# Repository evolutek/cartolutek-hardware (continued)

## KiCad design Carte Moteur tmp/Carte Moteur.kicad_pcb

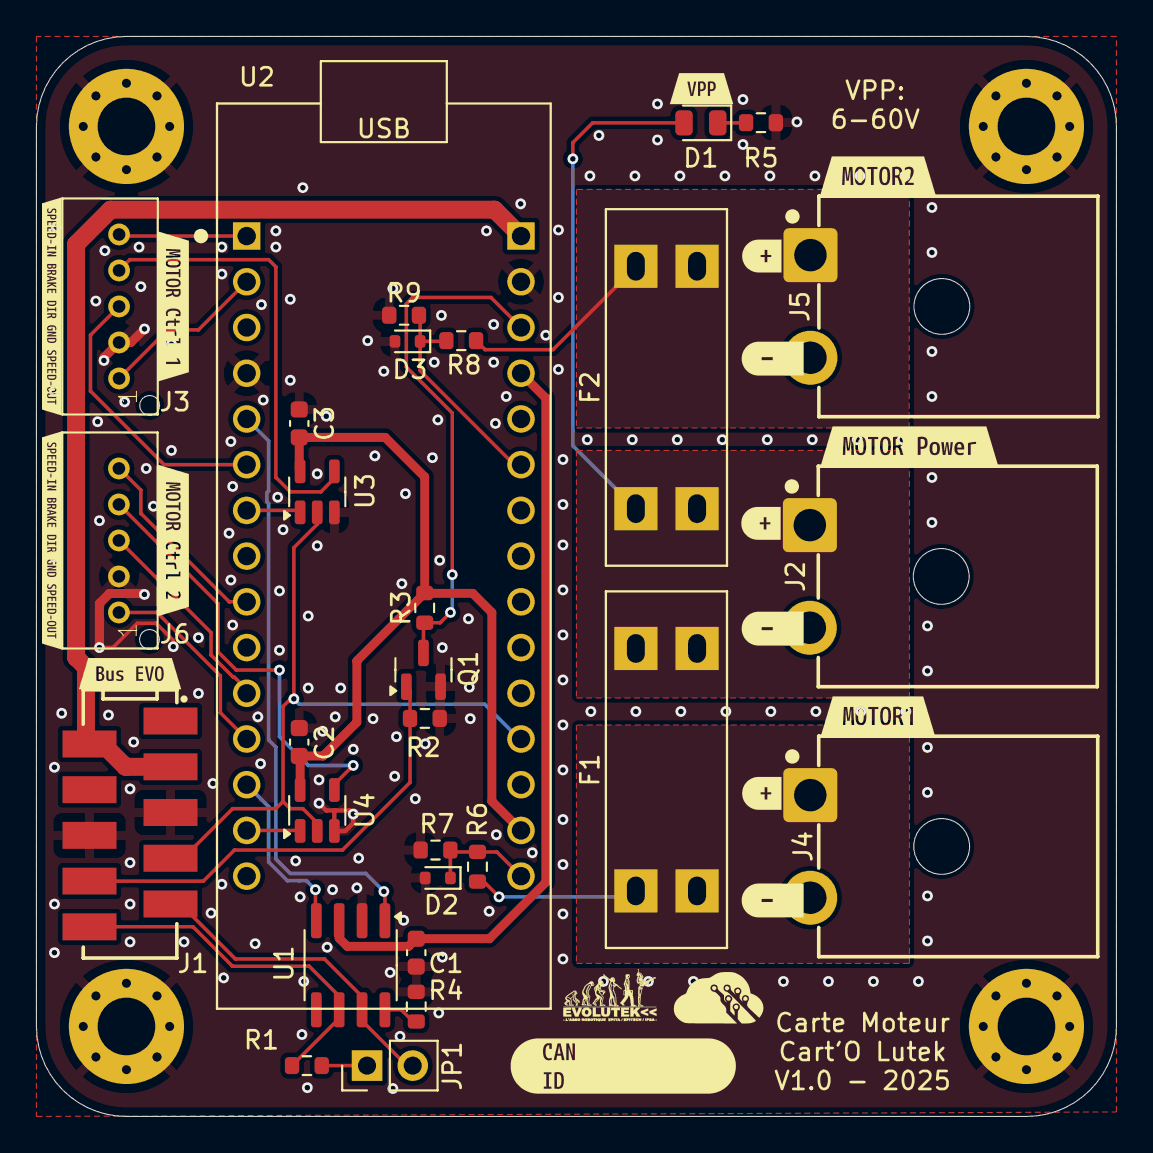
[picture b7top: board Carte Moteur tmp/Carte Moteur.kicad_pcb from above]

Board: 2 copper layers, 60.0 x 60.0 mm, 51 parts (0 on the bottom side), 29 nets.

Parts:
C1, C2, C3: 100nF; C_0603_1608Metric
D1: LED; LED_0805_2012Metric
D2, D3: 3V; D_SOD-523
F1, F2: To determine; FUSE_3557-2
H1, H2, H3, H4: M3; MountingHole_3.2mm_M3_Pad_Via
J1: Bus EVO; 690367281076
J2: Motor PSU; 657002140101
J3, J6: Motor Control; B05B-PASK
J4, J5: Motor; 657002140101
JP1: Jumper_2_Open; PinHeader_1x02_P2.54mm_Vertical
LB1: LOGO; logo-evo-micro
LB2: CAN ID Label
LB3: LOGO; Logo Aisler Micro
Q1: Q_NMOS_GSD; SOT-23
R1: 120; R_0603_1608Metric
R2, R3, R7, R9: 10k; R_0603_1608Metric
R4: 0; R_0603_1608Metric
R5: 2.1k; R_0603_1608Metric
R6, R8: 100k; R_0603_1608Metric
U1: MCP2551-I-SN; SOIC-8_3.9x4.9mm_P1.27mm
U2: NUCLEO-G431KB; MODULE_NUCLEO-32
U3, U4: SN74LVC1G32; SOT-23-5
kibuzzard-6849F6E8: G***; kibuzzard-6849F6E8
kibuzzard-6849F8B2: G***; kibuzzard-6849F8B2
kibuzzard-6849F8DE: G***; kibuzzard-6849F8DE
kibuzzard-6849F74E: G***; kibuzzard-6849F74E
kibuzzard-6849F710: G***; kibuzzard-6849F710
kibuzzard-6849F726: G***; kibuzzard-6849F726
kibuzzard-6849FC70, kibuzzard-6849FC70#2, kibuzzard-6849FC70#3: G***; kibuzzard-6849FC70
kibuzzard-6849FC90, kibuzzard-6849FC90#2, kibuzzard-6849FC90#3: G***; kibuzzard-6849FC90
kibuzzard-6849FDBB: G***; kibuzzard-6849FDBB
kibuzzard-6849FECA, kibuzzard-6849FECA#2: G***; kibuzzard-6849FECA

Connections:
+3.3V: C2.1, C3.1, R3.1, U2.2.14 (3.3V), U3.5 (VCC), U4.5 (VCC)
+5V: C1.1, U1.3 (VDD), U2.2.4 (5V)
+5V IN: J1.2, J1.3, U2.2.1 (VIN)
/AU: J1.7, U2.2.12 (PA0), U3.2 (B), U4.2 (B)
/BRAKE1: U2.1.7 (PB7), U3.1 (A)
/BRAKE2: U2.1.14 (PB5), U4.1 (A)
/CANH: J1.9, JP1.2 (B), U1.7 (CANH)
/CANL: J1.10, R1.1, U1.6 (CANL)
/CANRX: U1.4 (RXD), U2.1.13 (PA11)
/CANTX: U1.1 (TXD), U2.1.5 (PA12)
/DIR1: J3.3, U2.1.6 (PB0)
/DIR2: J6.3, U2.1.11 (PF1)
/PC1: D2.1 (K), R6.1, R7.1, U2.2.15 (PB3)
/PC2: D3.1 (K), R8.1, R9.2, U2.2.6 (PA7)
/RST: J1.8, Q1.1 (G), R2.1
/S1: J3.5, U2.1.1 (PA9)
/S2: J6.5, U2.1.9 (PB6)
/SPEED1: J3.1, U2.1.2 (PA10)
/SPEED2: J6.1, U2.1.12 (PA8)
/~RST: Q1.3 (D), R3.2, U2.2.3 (~RST)
GND: C1.2, C2.2, C3.2, D2.2 (A), D3.2 (A), H1.1, H2.1, H3.1, H4.1, J1.5, J1.6, J2.2, J3.2, J4.2, J5.2, J6.2, Q1.2 (S), R2.2, R4.2, R5.1, R7.2, R9.1, U1.2 (VSS), U2.1.4 (GND), U2.2.2 (GND), U3.3 (GND), U4.3 (GND)
unnamed: D1.1 (K), R5.2
unnamed: J3.4, U3.4 (S)
unnamed: J6.4, U4.4 (S)
unnamed: JP1.1 (A), R1.2
unnamed: R4.1, U1.8 (Rs)
VPP: D1.2 (A), F1.1, F2.1, J2.1
VPP MOTOR 1: F1.2, J4.1, R6.2
VPP MOTOR 2: F2.2, J5.1, R8.2

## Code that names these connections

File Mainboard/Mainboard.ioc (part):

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Mcu.Name=STM32G491K(C-E)Ux
Mcu.Package=UFQFPN32
Mcu.UserName=STM32G491KEUx
PA0.GPIOParameters=GPIO_Label
PA0.GPIO_Label=BATTERY_VOLTAGE
PA0.Mode=IN1-Single-Ended
PA0.Signal=ADC1_IN1
PA1.GPIOParameters=GPIO_Label
PA1.GPIO_Label=EMMERGENCY_STOP
PA1.Signal=GPXTI1
PA10.GPIOParameters=GPIO_Label
PA10.GPIO_Label=STATUS
PA10.Signal=GPIO_Output
PA11.Mode=Device
PA11.Signal=USB_DM
PA12.Mode=Device
PA12.Signal=USB_DP
PA13.Mode=Serial_Wire
PA13.Signal=SYS_JTMS-SWDIO
PA14.Mode=Serial_Wire
PA14.Signal=SYS_JTCK-SWCLK
PA15.GPIOParameters=GPIO_Label
PA15.GPIO_Label=WARNING_LIGHTS
PA15.Signal=S_TIM8_CH1
PA2.GPIOParameters=GPIO_Label
PA2.GPIO_Label=VCP_TX
PA2.Mode=Asynchronous
PA2.Signal=USART2_TX
PA3.GPIOParameters=GPIO_Label
PA3.GPIO_Label=VCP_RX
PA3.Mode=Asynchronous
PA3.Signal=USART2_RX
PA4.GPIOParameters=GPIO_Label
PA4.GPIO_Label=BUZZER
PA4.Signal=COMP_DAC11_group
PA5.GPIOParameters=GPIO_Label
PA5.GPIO_Label=HEADLIGHT
PA5.Signal=S_TIM2_CH1
PA6.GPIOParameters=GPIO_Label
PA6.GPIO_Label=MOTOR_POWER_ENABLE
PA6.Signal=GPIO_Output
PA7.GPIOParameters=GPIO_Label
PA7.GPIO_Label=MANUAL_MODE_ENABLE
PA7.Signal=GPIO_Output
PA8.Mode=I2C
PA8.Signal=I2C2_SDA
PA9.Mode=I2C
PA9.Signal=I2C2_SCL
PB0.GPIOParameters=GPIO_Label
PB0.GPIO_Label=MOTOR_POWER_SWITCH
PB0.Signal=GPXTI0
PB3.GPIOParameters=GPIO_Label
PB3.GPIO_Label=MANUAL_MODE_SWITCH
PB3.Signal=GPXTI3
PB4.GPIOParameters=GPIO_Label
PB4.GPIO_Label=LEDSTRIP_FRONT
PB4.Signal=S_TIM3_CH1
PB5.Mode=FDCAN_Activate
PB5.Signal=FDCAN2_RX
PB6.Mode=FDCAN_Activate
PB6.Signal=FDCAN2_TX
PB7.GPIOParameters=GPIO_Label
PB7.GPIO_Label=LEDSTRIP_BACK
PB7.Signal=S_TIM4_CH2
RCC.HSE_VALUE=8000000
RCC.SYSCLKFreq_VALUE=16000000
board=custom

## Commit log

2025-05-11 Carte moteur à review
2025-05-18 Correctifs carte moteur
2025-06-10 Correctifs pour review finale
2025-06-11 Release V1.0
2025-10-26 Add schematics
2025-12-03 WIP Schematics
2025-12-06 Schematics almost done
2025-12-06 Update footprints and correct minor mistakes
2025-12-06 add stm32cubeMx and composent place on the pcb
    add stm32cubeMx and composent place on the pcb
2025-12-06 WIP RPI Interface
2025-12-09 V1.0 of RPI Interface
2025-12-13 V1.0
2025-12-19 Schematics for UI Interface
2025-12-19 Update schematics
2025-12-23 WIP hoop interface
2025-12-23 Export schematics
2025-12-24 Rename folder to tmp name
2025-12-24 Rename folder to correct name
2025-12-24 Rename files
2026-01-02 Minor fixes
2026-01-02 Hoop Interface V1.0
2026-01-03 RPI Interface V1.0
2026-01-03 UI Interface V1.0
2026-01-03 Re-export STEP
2026-01-04 Remove trash file
2026-01-04 Minor fix in the schematics
2026-01-04 Fix bad reference
2026-01-05 Update res value
2026-01-06 Schematics before routing
2026-01-06 Fix schematics
2026-01-06 Minor fixes and pre-placement
2026-01-06 Minor fixes in schematics
2026-01-06 WIP routing
2026-01-08 Fix silkscreen
2026-01-09 Redesign power decoupling for VCC and VPP
2026-01-19 WIP PCB
2026-01-19 Rounting done
2026-01-19 Mainboard V1.0
